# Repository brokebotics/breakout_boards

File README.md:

# breakout_boards
Collection of breakout boards

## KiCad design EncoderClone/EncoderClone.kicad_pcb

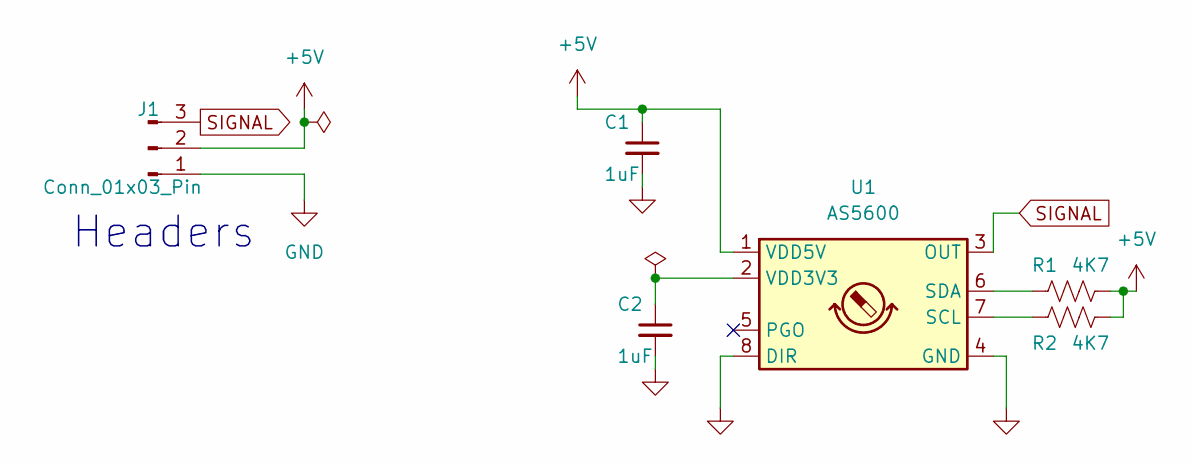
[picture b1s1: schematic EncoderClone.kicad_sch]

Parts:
C1, C2: 1uF; C_0402_1005Metric_Pad0.74x0.62mm_HandSolder; MPN C908010; JLCPCB Part # C5189823
J1: Conn_01x03_Pin; PinHeader_1x03_P2.54mm_Horizontal; MPN C2883841
R1, R2: 4K7; R_0402_1005Metric_Pad0.72x0.64mm_HandSolder; MPN C2692735; JLCPCB Part # C25900
U1: AS5600; SOIC-8_3.9x4.9mm_P1.27mm; MPN C499458; JLCPCB Part # C499458

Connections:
+5V: C1.1, J1.2, R1.2, R2.2, U1.1 (VDD5V)
GND: C1.2, C2.2, J1.1, U1.4 (GND), U1.8 (DIR)
unnamed: R2.1, U1.7 (SCL)
unnamed: R1.1, U1.6 (SDA)
unnamed: C2.1, U1.2 (VDD3V3)
SIGNAL: J1.3, U1.3 (OUT)

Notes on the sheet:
Headers

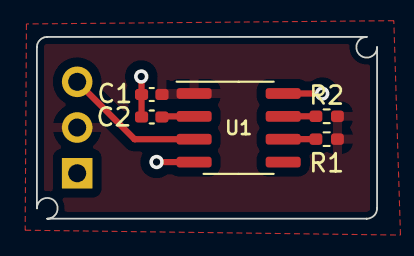
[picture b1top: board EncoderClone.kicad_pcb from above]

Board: 2 copper layers, 18.9 x 10.1 mm, 6 parts (1 on the bottom side), 6 nets.

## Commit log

2023-11-23 Added CTRE PWM Breakout
2024-09-16 Added additional breakout boards
2024-09-16 Folder cleanup
